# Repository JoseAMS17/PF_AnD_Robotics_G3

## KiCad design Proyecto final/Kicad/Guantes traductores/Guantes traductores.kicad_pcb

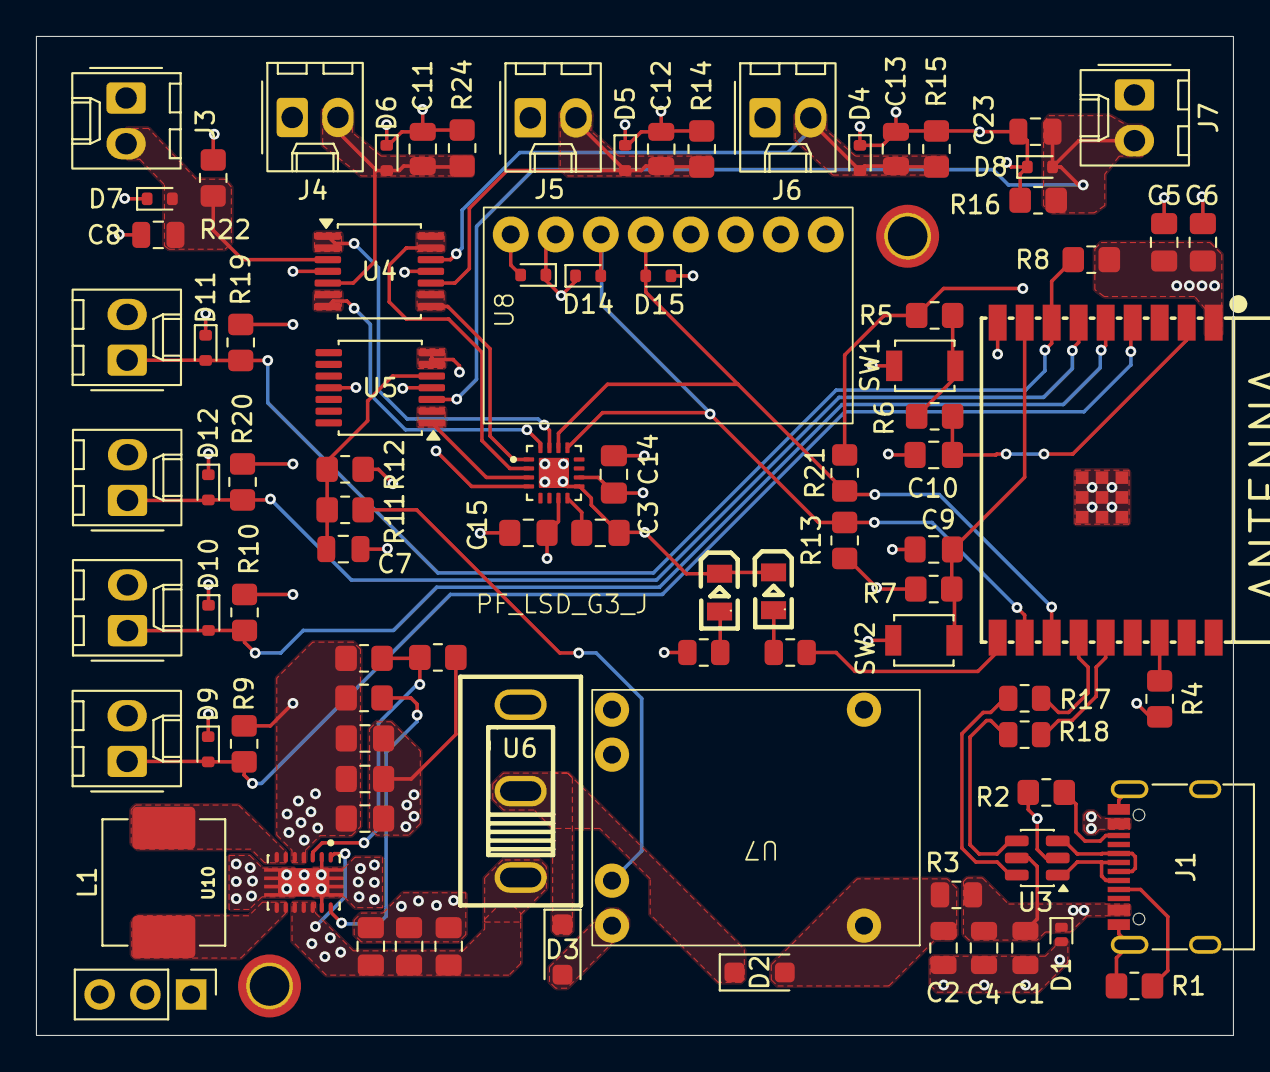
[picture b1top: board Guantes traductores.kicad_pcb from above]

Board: 4 copper layers, 66.5 x 55.5 mm, 92 parts (0 on the bottom side), 46 nets.

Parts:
C1, C2: 4.7u; C_0805_2012Metric
C3, C14, C15: 1uF; C_0805_2012Metric_Pad1.18x1.45mm_HandSolder
C4: 100nF; C_0805_2012Metric
C5: 4.7uF; C_0805_2012Metric_Pad1.18x1.45mm_HandSolder
C6, C9, C10: 100nF; C_0805_2012Metric_Pad1.18x1.45mm_HandSolder
C7, C8, C11, C12, C13, C23: 0.1uF; C_0805_2012Metric
C16, C17: 10uf; C_0805_2012Metric_Pad1.18x1.45mm_HandSolder
C18: 100nf; C_0805_2012Metric_Pad1.18x1.45mm_HandSolder
C19, C20, C21: 22uf; C_0805_2012Metric_Pad1.18x1.45mm_HandSolder
D1: PESD5V0L1ULD; D_SOD-882D
D2, D3: SMD26PL-TP; D_SOD-123F
D4, D5, D6, D7, D8, D9, D10, D11, D12, D13, D14, D15: ESD5B5.0ST1G; D_SOD-523
H1, H2: MountingHole_2.2mm_M2_ISO7380_Pad_TopOnly
J1: USB_C_Receptacle_USB2.0_16P; USB_C_Receptacle_G-Switch_GT-USB-7010ASV
J2: Conn_01x03_Pin; PinHeader_1x03_P2.54mm_Vertical
J3: Flex1; Molex_KK-254_AE-6410-02A_1x02_P2.54mm_Vertical
J4: Flex2; Molex_KK-254_AE-6410-02A_1x02_P2.54mm_Vertical
J5: Flex3; Molex_KK-254_AE-6410-02A_1x02_P2.54mm_Vertical
J6: Flex4; Molex_KK-254_AE-6410-02A_1x02_P2.54mm_Vertical
J7: Flex5; Molex_KK-254_AE-6410-02A_1x02_P2.54mm_Vertical
J10: Contacto1; Molex_KK-254_AE-6410-02A_1x02_P2.54mm_Vertical
J11: Contacto2; Molex_KK-254_AE-6410-02A_1x02_P2.54mm_Vertical
J12: Contacto3; Molex_KK-254_AE-6410-02A_1x02_P2.54mm_Vertical
J13: Contacto4; Molex_KK-254_AE-6410-02A_1x02_P2.54mm_Vertical
L1: 1.5uH; L_APV_APH0630
LED1: Green; C2297_LED0805-R-RD
LED2: Yellow; C2297_LED0805-R-RD
R1, R2, R13, R21: 5.1k; R_0805_2012Metric_Pad1.20x1.40mm_HandSolder
R3: 0R; R_0805_2012Metric
R4, R5, R7, R8, R9, R10, R11, R12, R19, R20: 10k; R_0805_2012Metric_Pad1.20x1.40mm_HandSolder
R6: 100; R_0805_2012Metric_Pad1.20x1.40mm_HandSolder
R14, R15, R16, R22, R24: 250k; R_0805_2012Metric_Pad1.20x1.40mm_HandSolder
R17, R18: 33; R_0805_2012Metric
R23, R26: 1M; R_0805_2012Metric_Pad1.20x1.40mm_HandSolder
R25: 180K; R_0805_2012Metric_Pad1.20x1.40mm_HandSolder
R28, R29: 200; R_0805_2012Metric
SW1, SW2: SW_SPST; SW_SPST_B3U-1000P
U1: ESP32-C3-WROOM-02; C2934560_BULETM-SMD_ESPRESSIF_ESP32-C3-WROOM-02-N4-4MB
U2: ADS7128IRTER; IC_ADS7128IRTER
U3: USBLC6-2SC6; SOT-23-6
U4, U5: LMV324; TSSOP-14_4.4x5mm_P0.65mm
U6: SS12D10G5; C7431054_SW-TH_SHOU-HAN_SS12D10G4
U7: TP4056 Board
U8: BNO055
U10: TPS63020DSJR; IC_TPS63020DSJR

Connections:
+3.3V: C5.1, C6.1, C14.1, C15.1, C19.1, C20.1, C21.1, D13.2, J2.3, J3.1, J4.1, J5.1, J6.1, J7.1, R4.2, R5.2, R7.2, R8.2, R9.2, R10.2, R13.2, R19.2, R20.2, R21.2, R23.1, R26.1, R28.2, U1.1 (3V3), U2.7 (AVDD), U2.10 (DVDD), U4.4 (V+), U5.4 (V+), U8.1 (VIN), U10.4 (VOUT_4), U10.5 (VOUT_5)
+5V: C2.1, D2.2 (A), R3.2, U7.1 (IN+)
/Ads7128/AIN0: U2.15 (AIN0/GPIO0), U4.1, U4.2 (-)
/Ads7128/AIN1: U2.16 (AIN1/GPIO1), U4.6 (-), U4.7
/Ads7128/AIN2: U2.1 (AIN2/GPIO2), U4.8, U4.9 (-)
/Ads7128/AIN3: U2.2 (AIN3/GPIO3), U4.13 (-), U4.14
/Ads7128/AIN4: U2.3 (AIN4/GPIO4), U5.1, U5.2 (-)
/Ads7128/AIN5: U2.4 (AIN5/GPIO5), U5.6 (-), U5.7
/Buckboost 3.7V-5V a 3.3V/Vin: C16.1, C17.1, C18.1, J2.1, U6.1, U10.1 (VINA), U10.10 (VIN_10), U10.11 (VIN_11), U10.12 (EN)
/Esp32 C3 WROOM-02/EN: C10.1, R6.1, U1.2 (EN)
/USB-C/D+: J1.A6 (D+), J1.B6 (D+), U3.3 (I/O2)
/USB-C/D-: J1.A7 (D-), J1.B7 (D-), U3.1 (I/O1)
/USB-C/R+: R18.1, U3.4 (I/O2)
/USB-C/R-: R17.1, U3.6 (I/O1)
GND: C1.2, C2.2, C3.2, C4.2, C5.2, C6.2, C7.1, C8.1, C9.2, C10.2, C11.1, C12.1, C13.1, C14.2, C15.2, C16.2, C17.2, C18.2, C19.2, C20.2, C21.2, C23.1, D1.2 (A), D4.1, D5.1, D6.1, D7.1, D8.1, D9.1, D10.1, D11.1, D12.1, D13.1, D14.1, D15.1, H1.1, H2.1, H2.2, J1.A1 (GND), J1.A12 (GND), J1.B1 (GND), J1.B12 (GND), J1.S1 (SHIELD), J2.2, J10.2, J11.2, J12.2, J13.2, LED1.2 (K), LED2.2 (K), R1.2, R2.2, R12.1, R14.1, R15.1, R16.1, R22.1, R24.1, R25.2, SW1.1 (A), SW2.1 (A), U1.9 (GND), U1.19 (GND), U2.9 (GND), U2.17 (GND), U3.2 (GND), U4.11 (V-), U5.11 (V-), U7.2 (IN-), U7.4 (OUT-), U8.2 (GND), U10.2 (GND), U10.13 (PS/SYNC), U10.15 (PGND)
I2C_SCL: D14.2, R13.1, U1.11 (IO20/RXD), U2.13 (SCL), U8.3 (SCL/Rx)
I2C_SDA: D15.2, R21.1, U1.12 (IO21/TXD), U2.14 (SDA), U8.4 (SDA/Tx)
IO2: R4.1, U1.16 (IO2)
IO5: D9.2, J10.1, R9.1, U1.4 (IO5)
IO6: D10.2, J11.1, R10.1, U1.5 (IO6)
IO7: D12.2, J12.1, R20.1, U1.6 (IO7)
IO8: D11.2, J13.1, R8.1, R19.1, U1.7 (IO8)
IO9: C9.1, R7.1, SW2.2 (B), U1.8 (IO9)
IO10: R29.2, U1.10 (IO10)
unnamed: C1.1, C4.1, D1.1 (K), J1.A4 (VBUS), J1.A9 (VBUS), J1.B4 (VBUS), J1.B9 (VBUS), R3.1, U3.5 (VBUS)
unnamed: D2.1 (K), D3.1 (K), U6.2
unnamed: D3.2 (A), U7.3 (OUT+)
unnamed: J1.A5 (CC1), R1.1
unnamed: J1.B5 (CC2), R2.1
unnamed: C8.2, D7.2, J3.2, R22.2, U4.3 (+)
unnamed: C11.2, D6.2, J4.2, R24.2, U4.5 (+)
unnamed: C12.2, D5.2, J5.2, R14.2, U4.10 (+)
unnamed: C13.2, D4.2, J6.2, R15.2, U4.12 (+)
unnamed: C23.2, D8.2, J7.2, R16.2, U5.3 (+)
unnamed: LED1.1 (A), R29.1
unnamed: LED2.1 (A), R28.1
unnamed: R5.1, R6.2, SW1.2 (B)
unnamed: C3.1, U2.8 (DECAP)
unnamed: C7.2, R11.1, R12.2, U5.5 (+)
unnamed: R23.2, R25.1, U10.3 (FB)
unnamed: L1.1, U10.8 (L1_8), U10.9 (L1_9)
unnamed: L1.2, U10.6 (L2_6), U10.7 (L2_7)
unnamed: R26.2, U10.14 (PG)
USB_D+: R18.2, U1.14 (IO19)
USB_D-: R17.2, U1.13 (IO18)
VBat: R11.2, U7.5 (BAT+)

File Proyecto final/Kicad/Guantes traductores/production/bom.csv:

Designator,Footprint,Quantity,Value,LCSC Part #
"C1, C2",0805,2,4.7u,
"C10, C18, C4, C6, C9",0805,5,100nF,
"C11, C12, C13, C23, C7, C8",0805,6,0.1uF,
"C14, C15, C3",0805,3,1uF,
"C16, C17",0805,2,10uf,
"C19, C20, C21",0805,3,22uf,
C5,0805,1,4.7uF,
D1,D_SOD-882D,1,PESD5V0L1ULD,
"D10, D11, D12, D13, D14, D15, D4, D5, D6, D7, D8, D9",D_SOD-523,12,ESD5B5.0ST1G,C93623
"D2, D3",D_SOD-123F,2,SMD26PL-TP,
J1,USB_C_Receptacle_G-Switch_GT-USB-7010ASV,1,USB_C_Receptacle_USB2.0_16P,
J10,Molex_KK-254_AE-6410-02A_1x02_P2.54mm_Vertical,1,Contacto1,
J11,Molex_KK-254_AE-6410-02A_1x02_P2.54mm_Vertical,1,Contacto2,
J12,Molex_KK-254_AE-6410-02A_1x02_P2.54mm_Vertical,1,Contacto3,
J13,Molex_KK-254_AE-6410-02A_1x02_P2.54mm_Vertical,1,Contacto4,
J2,PinHeader_1x03_P2.54mm_Vertical,1,Conn_01x03_Pin,
J3,Molex_KK-254_AE-6410-02A_1x02_P2.54mm_Vertical,1,Flex1,
J4,Molex_KK-254_AE-6410-02A_1x02_P2.54mm_Vertical,1,Flex2,
J5,Molex_KK-254_AE-6410-02A_1x02_P2.54mm_Vertical,1,Flex3,
J6,Molex_KK-254_AE-6410-02A_1x02_P2.54mm_Vertical,1,Flex4,
J7,Molex_KK-254_AE-6410-02A_1x02_P2.54mm_Vertical,1,Flex5,
L1,L_APV_APH0630,1,1.5uH,
LED1,C2297_LED0805-R-RD,1,Green,C2297
LED2,C2297_LED0805-R-RD,1,Yellow,C2297
"R1, R13, R2, R21",0805,4,5.1k,
"R10, R11, R12, R19, R20, R4, R5, R7, R8, R9",0805,10,10k,
"R14, R15, R16, R22, R24",0805,5,250k,
"R17, R18",0805,2,33,
"R23, R26",0805,2,1M,
R25,0805,1,180K,
"R28, R29",0805,2,200,
R3,0805,1,0R,
R6,0805,1,100,
"SW1, SW2",SW_SPST_B3U-1000P,2,SW_SPST,
U1,C2934560_BULETM-SMD_ESPRESSIF_ESP32-C3-WROOM-02-N4-4MB,1,ESP32-C3-WROOM-02,C2934560
U10,IC_TPS63020DSJR,1,TPS63020DSJR,
U2,IC_ADS7128IRTER,1,ADS7128IRTER,
U3,SOT-23-6,1,USBLC6-2SC6,
"U4, U5",TSSOP-14_4.4x5mm_P0.65mm,2,LMV324,
U6,C7431054_SW-TH_SHOU-HAN_SS12D10G4,1,SS12D10G5,C7431054
U7,TP4056 Board,1,TP4056 Board,
U8,BNO055,1,BNO055,

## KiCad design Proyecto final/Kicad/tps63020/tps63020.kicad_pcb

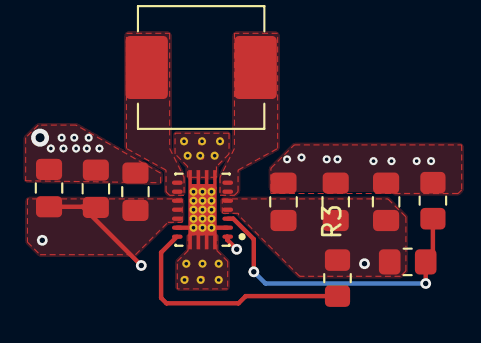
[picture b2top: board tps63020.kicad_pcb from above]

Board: 4 copper layers, 11 parts (0 on the bottom side), 7 nets.

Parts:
C1, C2: 10uf; C_0805_2012Metric_Pad1.18x1.45mm_HandSolder
C3: 100nf; C_0805_2012Metric_Pad1.18x1.45mm_HandSolder
C4, C5, C6: 22uf; C_0805_2012Metric_Pad1.18x1.45mm_HandSolder
L1: 1.5uH; L_APV_APH0630
R1, R3: 1M; R_0805_2012Metric_Pad1.20x1.40mm_HandSolder
R2: 180K; R_0805_2012Metric_Pad1.20x1.40mm_HandSolder
U2: TPS63020DSJR

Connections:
+3V3: C4.1, C5.1, C6.1, R1.1, R3.1, U2.4 (VOUT_4), U2.5 (VOUT_5)
GND: C1.2, C2.2, C3.2, C4.2, C5.2, C6.2, R2.2, U2.2 (GND), U2.13 (PS/SYNC), U2.15 (PGND), U2.16, U2.17, U2.18, U2.19, U2.20, U2.21, U2.22, U2.23, U2.24, U2.25, U2.26, U2.27, U2.28, U2.29, U2.30
unnamed: R1.2, R2.1, U2.3 (FB)
unnamed: L1.1, U2.8 (L1_8), U2.9 (L1_9)
unnamed: L1.2, U2.6 (L2_6), U2.7 (L2_7)
unnamed: R3.2, U2.14 (PG)
VBAT: C1.1, C2.1, C3.1, U2.1 (VINA), U2.10 (VIN_10), U2.11 (VIN_11), U2.12 (EN)

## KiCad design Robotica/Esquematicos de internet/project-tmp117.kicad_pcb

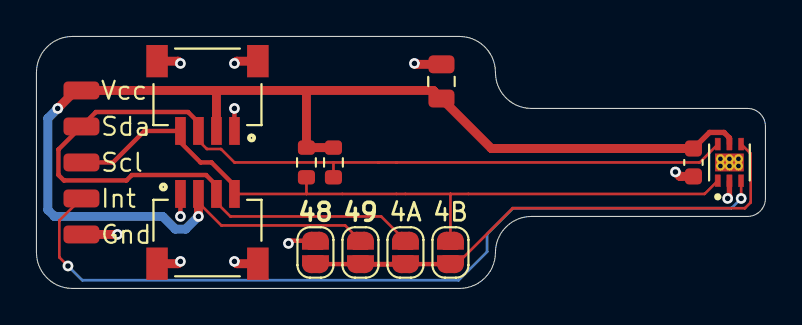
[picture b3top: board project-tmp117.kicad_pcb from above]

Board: 2 copper layers, 40.5 x 14.0 mm, 16 parts (0 on the bottom side), 6 nets.

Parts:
C1: 0.1uF; C_0603_1608Metric
C2: 4.7uF; C_0805_2012Metric
J1, J2, J3, J4, J5: Conn_01x01_Pin; SolderWirePad_1x01_SMD_1x2mm
J7, J8: SM04B-SRSS-TB(LF)(SN); JST_SM04B-SRSS-TB(LF)(SN)
JP1: 49; SolderJumper-2_P1.3mm_Open_RoundedPad1.0x1.5mm
JP2: 4A; SolderJumper-2_P1.3mm_Open_RoundedPad1.0x1.5mm
JP3: 4B; SolderJumper-2_P1.3mm_Open_RoundedPad1.0x1.5mm
JP4: 48; SolderJumper-2_P1.3mm_Open_RoundedPad1.0x1.5mm
R2, R4: 10k; R_0603_1608Metric
U1: TMP117AIDRVR; SON65P200X200X80-7N

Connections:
/ADD0: JP1.1 (A), JP2.1 (A), JP3.1 (A), JP4.1 (A), U1.4 (ADD0)
/INT: J4.1, U1.3 (ALERT)
/SCL: J3.1, J7.4, J8.4, JP3.2 (B), R4.2, U1.1 (SCL)
/SDA: J2.1, J7.3, J8.3, JP2.2 (B), R2.2, U1.6 (SDA)
GND: C1.2, C2.2, J5.1, J7.1, J7.S1 (SHIELD), J7.S2 (SHIELD), J8.1, J8.S1 (SHIELD), J8.S2 (SHIELD), JP4.2 (B), U1.2 (GND)
VCC: C1.1, C2.1, J1.1, J7.2, J8.2, JP1.2 (B), R2.1, R4.1, U1.5 (V+)

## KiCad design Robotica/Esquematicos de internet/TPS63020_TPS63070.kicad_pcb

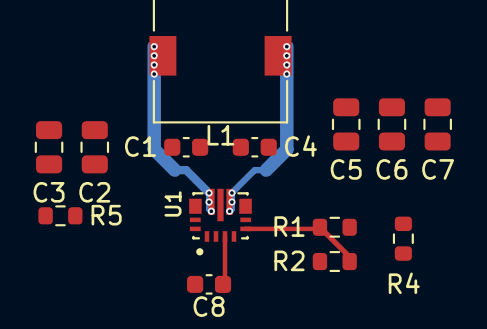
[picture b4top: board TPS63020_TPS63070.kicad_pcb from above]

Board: 2 copper layers, 14 parts (0 on the bottom side), 9 nets.

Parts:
C1, C4: 10uF; C_0603_1608Metric
C2, C3: 10uF; C_0805_2012Metric
C5, C6, C7: 22uF; C_0805_2012Metric
C8: 100nF; C_0603_1608Metric
L1: 1.5uH; L_7.3x7.3_H3.5
R1: _R1; R_0603_1608Metric
R2: _R2; R_0603_1608Metric
R4: 100K; R_0603_1608Metric
R5: 10K; R_0603_1608Metric
U1: TPS63070RNMR; VREG_TPS63070RNMR

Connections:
+3.3V: C4.1, C5.1, C6.1, C7.1, R1.2, R4.1, U1.7_8 (VOUT)
FB: R1.1, R2.2, U1.5 (FB)
GND: C1.2, C2.2, C3.2, C4.2, C5.2, C6.2, C7.2, C8.2, R2.1, U1.4 (GND), U1.6 (FB2), U1.10 (PGND), U1.15 (VSEL)
unnamed: R5.2, U1.1 (PS/SYNC), U1.14 (EN)
unnamed: L1.2, U1.11 (L1)
unnamed: L1.1, U1.9 (L2)
unnamed: R4.2, U1.2 (PG)
unnamed: C8.1, U1.3 (VAUX)
VCC: C1.1, C2.1, C3.1, R5.1, U1.12_13 (VIN)
